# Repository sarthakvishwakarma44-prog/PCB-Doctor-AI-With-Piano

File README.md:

# PCB-Doctor-AI With Piano.
<hr>
<h4>Here i had created a PCB doctor AI with piano, here this was able to do DRC and ERC of PCB and also able to describe the component of PCB's.</h4>
<br><h4>Here this was able to do this things.-</h4>
<ul>
  <li>DRC of physical PCB's.</li>
  <li>ERC of physical PCB's.</li>
  <li>Describe about Components.</li>
  <li>A piano which plays automatic.</li>
</ul>
<hr>
<p><h4>And there is it's source image.-</h4></p>
<h3>Piano</h3>

<hr>
<h3>Servo motor</h3>

<hr>
<h3>PCB's of Camera.</h3>

<hr>

<hr>

<hr>

<hr>

<hr>
<h3>Main Structure</h3>

<hr>
<p><h4>I have less information of KiCad that's why i use google mean they guide me that how to work and i am doing like that. All the PCB's design i have done under the guidance of Google. And for code i have also write it under the guidance of Google.</h4></p>
<br><p><h4>This is work like when we put the PCB in the stand then the camera detect and make imaginary Software PCB and they will done there DRC and ERC in there software and tell the fault in the design of PCB's.</h4></p>
<br><p><h4>And then there is automatic playable piano which was able to play any song automatic without pressing any key by our hands. And we will add SD card to Play any song in it.</h4></p>
<hr>
<p>One more important thing was that i have no 3D printer but my friend live in Honk Kong have this, so my friend will be order all the PCB's in there place and they will also build it there.</p>

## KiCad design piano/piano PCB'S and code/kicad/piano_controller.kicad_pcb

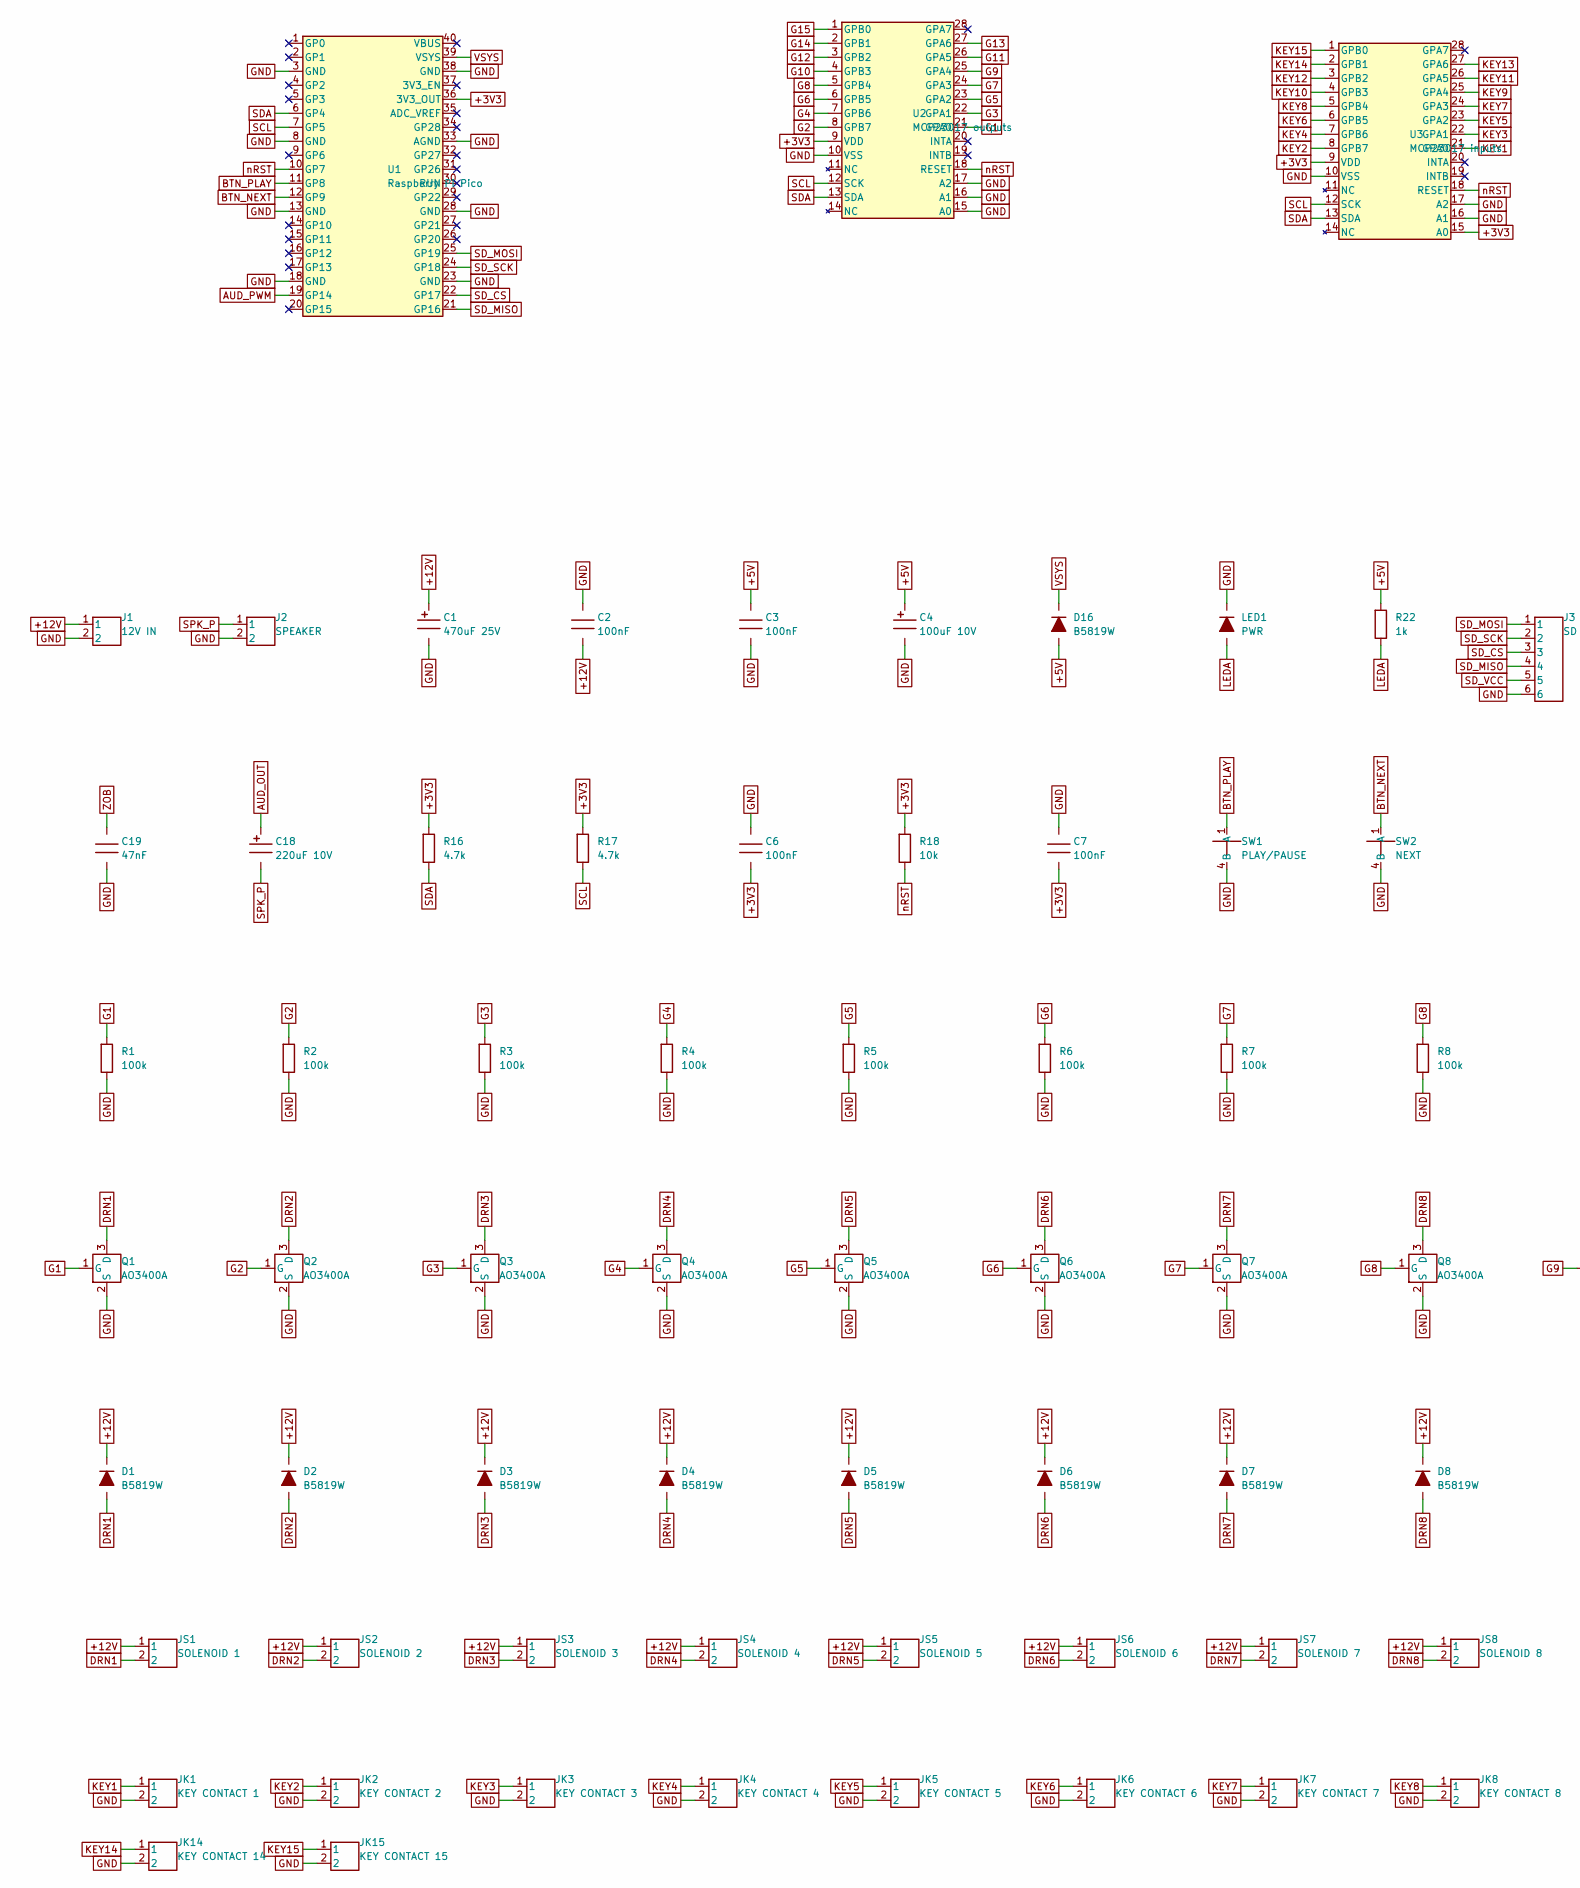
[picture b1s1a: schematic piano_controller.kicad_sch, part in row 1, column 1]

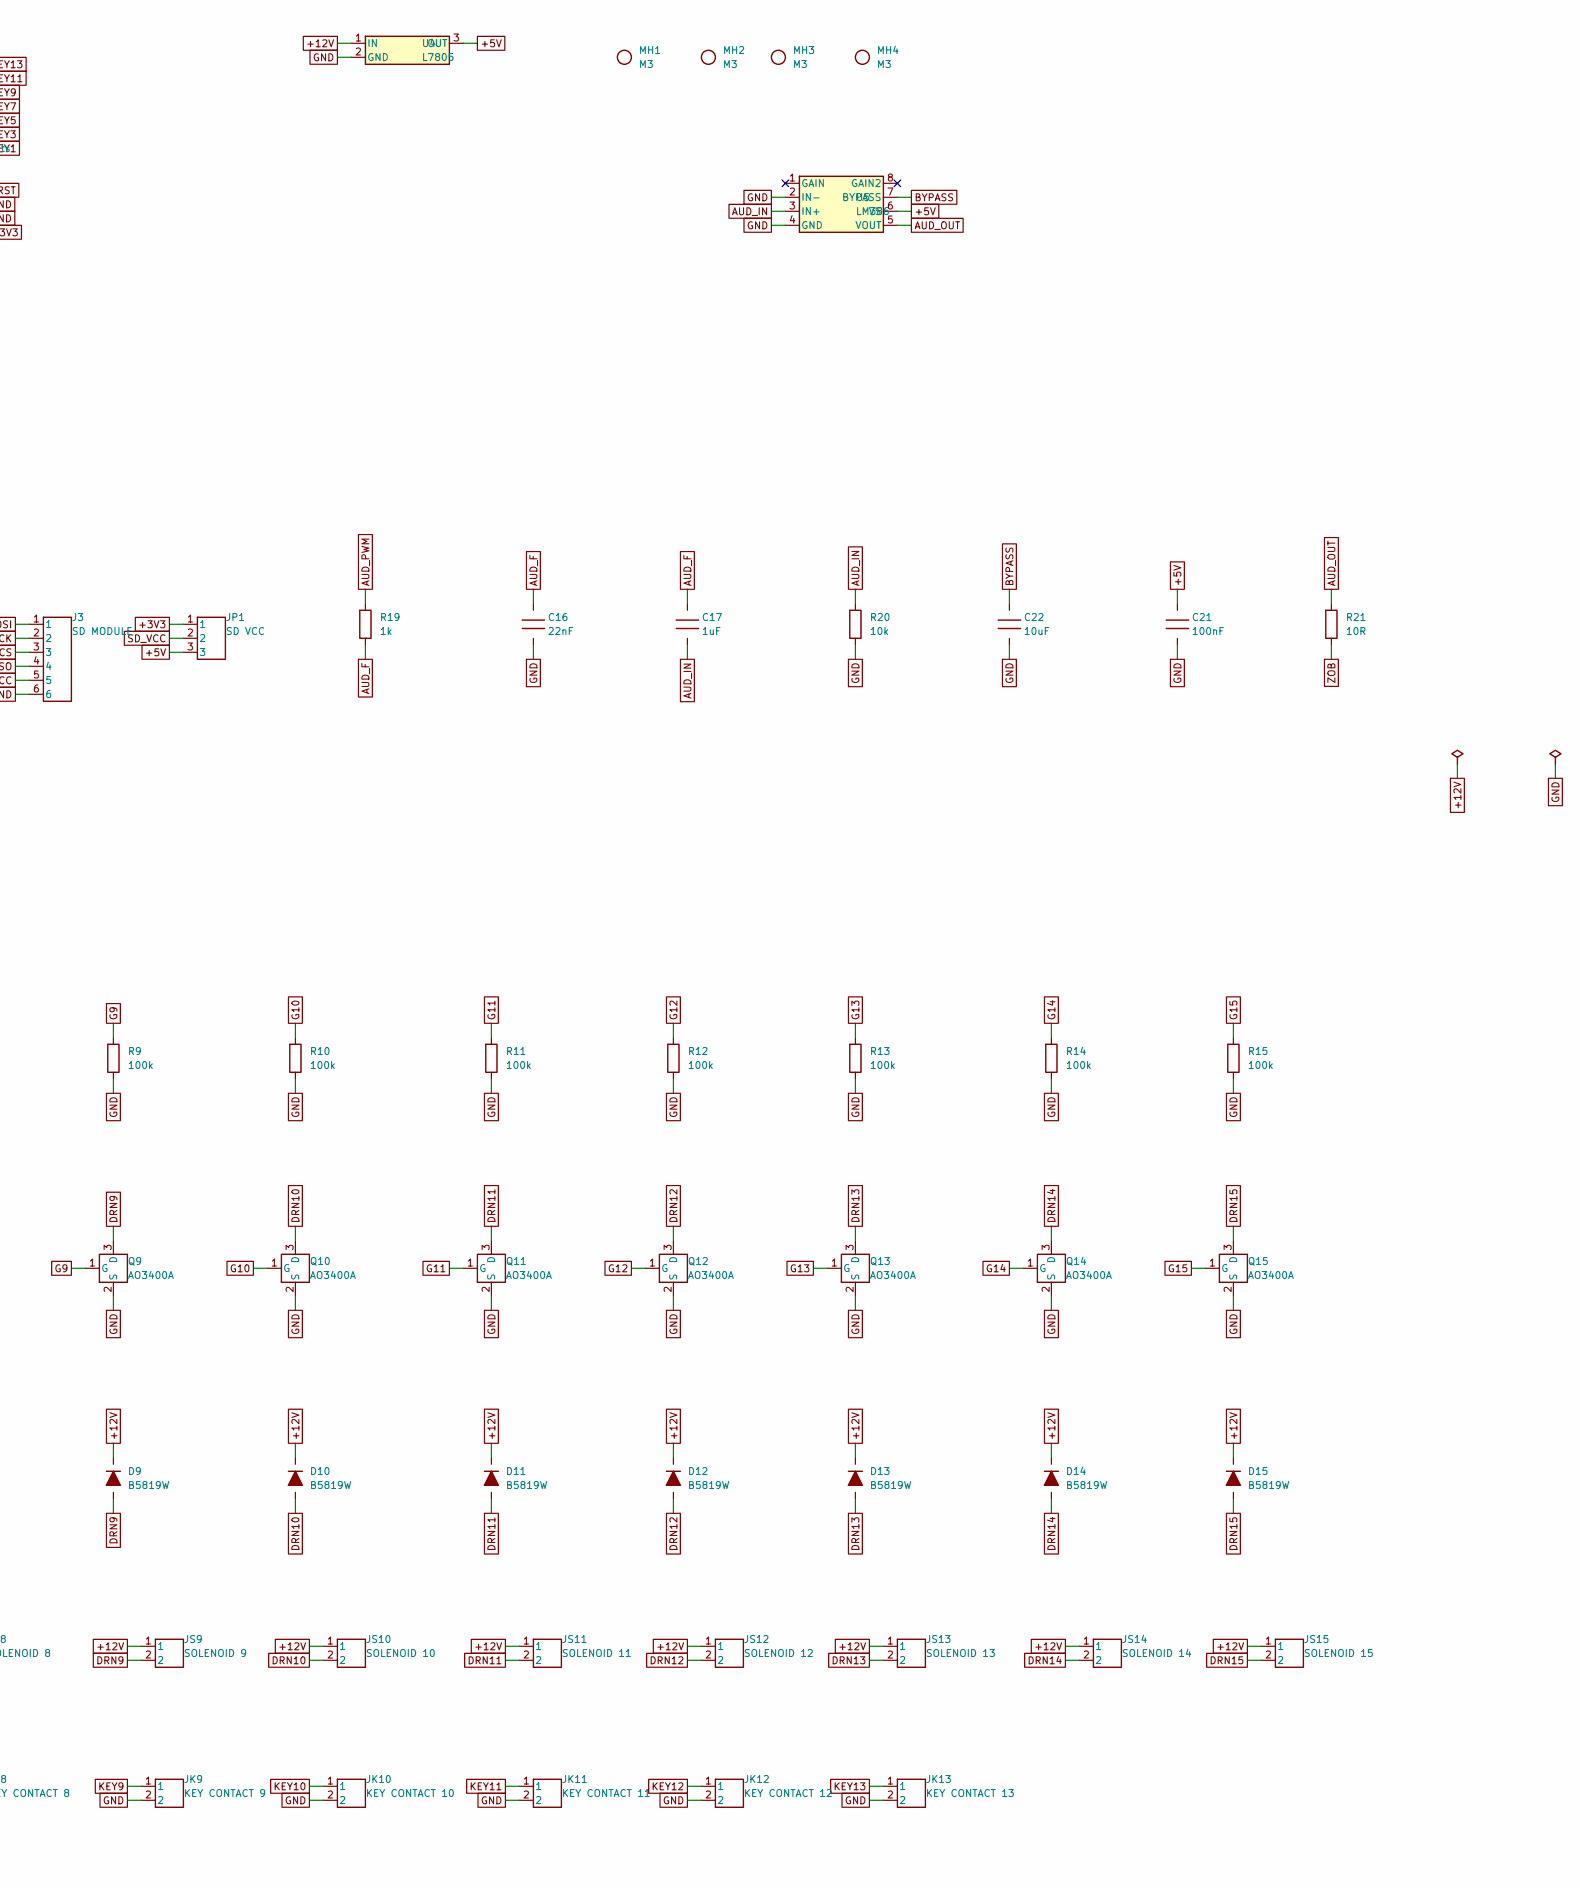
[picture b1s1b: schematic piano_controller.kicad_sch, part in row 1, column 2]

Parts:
C1: 470uF 25V; CP_Radial_D8.0mm_P3.50mm
C2, C3, C6, C7, C21: 100nF; C_0603
C4: 100uF 10V; CP_Radial_D5.0mm_P2.00mm
C16: 22nF; C_0603
C17: 1uF; C_0603
C18: 220uF 10V; CP_Radial_D6.3mm_P2.50mm
C19: 47nF; C_0603
C22: 10uF; C_0603
D1, D2, D3, D4, D5, D6, D7, D8, D9, D10, D11, D12, D13, D14, D15, D16: B5819W; D_SOD-123
J1: 12V IN; TerminalBlock_2P_P5.08mm
J2: SPEAKER; TerminalBlock_2P_P5.08mm
J3: SD MODULE; PinHeader_1x06_P2.54mm
JK1: KEY CONTACT 1; PinHeader_1x02_P2.54mm
JK2: KEY CONTACT 2; PinHeader_1x02_P2.54mm
JK3: KEY CONTACT 3; PinHeader_1x02_P2.54mm
JK4: KEY CONTACT 4; PinHeader_1x02_P2.54mm
JK5: KEY CONTACT 5; PinHeader_1x02_P2.54mm
JK6: KEY CONTACT 6; PinHeader_1x02_P2.54mm
JK7: KEY CONTACT 7; PinHeader_1x02_P2.54mm
JK8: KEY CONTACT 8; PinHeader_1x02_P2.54mm
JK9: KEY CONTACT 9; PinHeader_1x02_P2.54mm
JK10: KEY CONTACT 10; PinHeader_1x02_P2.54mm
JK11: KEY CONTACT 11; PinHeader_1x02_P2.54mm
JK12: KEY CONTACT 12; PinHeader_1x02_P2.54mm
JK13: KEY CONTACT 13; PinHeader_1x02_P2.54mm
JK14: KEY CONTACT 14; PinHeader_1x02_P2.54mm
JK15: KEY CONTACT 15; PinHeader_1x02_P2.54mm
JP1: SD VCC; PinHeader_1x03_P2.54mm
JS1: SOLENOID 1; PinHeader_1x02_P2.54mm
JS2: SOLENOID 2; PinHeader_1x02_P2.54mm
JS3: SOLENOID 3; PinHeader_1x02_P2.54mm
JS4: SOLENOID 4; PinHeader_1x02_P2.54mm
JS5: SOLENOID 5; PinHeader_1x02_P2.54mm
JS6: SOLENOID 6; PinHeader_1x02_P2.54mm
JS7: SOLENOID 7; PinHeader_1x02_P2.54mm
JS8: SOLENOID 8; PinHeader_1x02_P2.54mm
JS9: SOLENOID 9; PinHeader_1x02_P2.54mm
JS10: SOLENOID 10; PinHeader_1x02_P2.54mm
JS11: SOLENOID 11; PinHeader_1x02_P2.54mm
JS12: SOLENOID 12; PinHeader_1x02_P2.54mm
JS13: SOLENOID 13; PinHeader_1x02_P2.54mm
JS14: SOLENOID 14; PinHeader_1x02_P2.54mm
JS15: SOLENOID 15; PinHeader_1x02_P2.54mm
LED1: PWR; LED_0603
MH1, MH2, MH3, MH4: M3; MountingHole_3.2mm_M3
Q1, Q2, Q3, Q4, Q5, Q6, Q7, Q8, Q9, Q10, Q11, Q12, Q13, Q14, Q15: AO3400A; SOT-23
R1, R2, R3, R4, R5, R6, R7, R8, R9, R10, R11, R12, R13, R14, R15: 100k; R_0603
R16, R17: 4.7k; R_0603
R18, R20: 10k; R_0603
R19, R22: 1k; R_0603
R21: 10R; R_0603
SW1: PLAY/PAUSE; SW_PUSH_6mm
SW2: NEXT; SW_PUSH_6mm
U1: Raspberry Pi Pico; RPi_Pico_Socket_2x20
U2: MCP23017 outputs; DIP-28_W7.62mm
U3: MCP23017 inputs; DIP-28_W7.62mm
U4: L7805; TO-220-3_Vertical
U5: LM386; DIP-8_W7.62mm

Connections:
+3V3: C6.2, C7.2, JP1.1, R16.1, R17.1, R18.1, U1.36 (3V3_OUT), U2.9 (VDD), U3.9 (VDD), U3.15 (A0)
+5V: C3.1, C4.1 (+), C21.1, D16.2 (A), JP1.3, R22.1, U4.3 (OUT), U5.6 (VS)
+12V: C1.1 (+), C2.2, D1.1 (K), D2.1 (K), D3.1 (K), D4.1 (K), D5.1 (K), D6.1 (K), D7.1 (K), D8.1 (K), D9.1 (K), D10.1 (K), D11.1 (K), D12.1 (K), D13.1 (K), D14.1 (K), D15.1 (K), J1.1, JS1.1, JS2.1, JS3.1, JS4.1, JS5.1, JS6.1, JS7.1, JS8.1, JS9.1, JS10.1, JS11.1, JS12.1, JS13.1, JS14.1, JS15.1, U4.1 (IN)
AUD_F: C16.1, C17.1, R19.2
AUD_IN: C17.2, R20.1, U5.3 (IN+)
AUD_OUT: C18.1 (+), R21.1, U5.5 (VOUT)
AUD_PWM: R19.1, U1.19 (GP14)
BTN_NEXT: SW2.1 (A), U1.12 (GP9)
BTN_PLAY: SW1.1 (A), U1.11 (GP8)
BYPASS: C22.1, U5.7 (BYPASS)
DRN1: D1.2 (A), JS1.2, Q1.3 (D)
DRN2: D2.2 (A), JS2.2, Q2.3 (D)
DRN3: D3.2 (A), JS3.2, Q3.3 (D)
DRN4: D4.2 (A), JS4.2, Q4.3 (D)
DRN5: D5.2 (A), JS5.2, Q5.3 (D)
DRN6: D6.2 (A), JS6.2, Q6.3 (D)
DRN7: D7.2 (A), JS7.2, Q7.3 (D)
DRN8: D8.2 (A), JS8.2, Q8.3 (D)
DRN9: D9.2 (A), JS9.2, Q9.3 (D)
DRN10: D10.2 (A), JS10.2, Q10.3 (D)
DRN11: D11.2 (A), JS11.2, Q11.3 (D)
DRN12: D12.2 (A), JS12.2, Q12.3 (D)
DRN13: D13.2 (A), JS13.2, Q13.3 (D)
DRN14: D14.2 (A), JS14.2, Q14.3 (D)
DRN15: D15.2 (A), JS15.2, Q15.3 (D)
G1: Q1.1 (G), R1.1, U2.21 (GPA0)
G2: Q2.1 (G), R2.1, U2.8 (GPB7)
G3: Q3.1 (G), R3.1, U2.22 (GPA1)
G4: Q4.1 (G), R4.1, U2.7 (GPB6)
G5: Q5.1 (G), R5.1, U2.23 (GPA2)
G6: Q6.1 (G), R6.1, U2.6 (GPB5)
G7: Q7.1 (G), R7.1, U2.24 (GPA3)
G8: Q8.1 (G), R8.1, U2.5 (GPB4)
G9: Q9.1 (G), R9.1, U2.25 (GPA4)
G10: Q10.1 (G), R10.1, U2.4 (GPB3)
G11: Q11.1 (G), R11.1, U2.26 (GPA5)
G12: Q12.1 (G), R12.1, U2.3 (GPB2)
G13: Q13.1 (G), R13.1, U2.27 (GPA6)
G14: Q14.1 (G), R14.1, U2.2 (GPB1)
G15: Q15.1 (G), R15.1, U2.1 (GPB0)
GND: C1.2 (-), C2.1, C3.2, C4.2 (-), C6.1, C7.1, C16.2, C19.2, C21.2, C22.2, J1.2, J2.2, J3.6, JK1.2, JK2.2, JK3.2, JK4.2, JK5.2, JK6.2, JK7.2, JK8.2, JK9.2, JK10.2, JK11.2, JK12.2, JK13.2, JK14.2, JK15.2, LED1.1 (K), Q1.2 (S), Q2.2 (S), Q3.2 (S), Q4.2 (S), Q5.2 (S), Q6.2 (S), Q7.2 (S), Q8.2 (S), Q9.2 (S), Q10.2 (S), Q11.2 (S), Q12.2 (S), Q13.2 (S), Q14.2 (S), Q15.2 (S), R1.2, R2.2, R3.2, R4.2, R5.2, R6.2, R7.2, R8.2, R9.2, R10.2, R11.2, R12.2, R13.2, R14.2, R15.2, R20.2, SW1.4 (B), SW2.4 (B), U1.3 (GND), U1.8 (GND), U1.13 (GND), U1.18 (GND), U1.23 (GND), U1.28 (GND), U1.33 (AGND), U1.38 (GND), U2.10 (VSS), U2.15 (A0), U2.16 (A1), U2.17 (A2), U3.10 (VSS), U3.16 (A1), U3.17 (A2), U4.2 (GND), U5.2 (IN-), U5.4 (GND)
KEY1: JK1.1, U3.21 (GPA0)
KEY2: JK2.1, U3.8 (GPB7)
KEY3: JK3.1, U3.22 (GPA1)
KEY4: JK4.1, U3.7 (GPB6)
KEY5: JK5.1, U3.23 (GPA2)
KEY6: JK6.1, U3.6 (GPB5)
KEY7: JK7.1, U3.24 (GPA3)
KEY8: JK8.1, U3.5 (GPB4)
KEY9: JK9.1, U3.25 (GPA4)
KEY10: JK10.1, U3.4 (GPB3)
KEY11: JK11.1, U3.26 (GPA5)
KEY12: JK12.1, U3.3 (GPB2)
KEY13: JK13.1, U3.27 (GPA6)
KEY14: JK14.1, U3.2 (GPB1)
KEY15: JK15.1, U3.1 (GPB0)
LEDA: LED1.2 (A), R22.2
SCL: R17.2, U1.7 (GP5), U2.12 (SCK), U3.12 (SCK)
SDA: R16.2, U1.6 (GP4), U2.13 (SDA), U3.13 (SDA)
SD_CS: J3.3, U1.22 (GP17)
SD_MISO: J3.4, U1.21 (GP16)
SD_MOSI: J3.1, U1.25 (GP19)
SD_SCK: J3.2, U1.24 (GP18)
SD_VCC: J3.5, JP1.2
SPK_P: C18.2 (-), J2.1
VSYS: D16.1 (K), U1.39 (VSYS)
ZOB: C19.1, R21.2
nRST: R18.2, U1.10 (GP7), U2.18 (RESET), U3.18 (RESET)

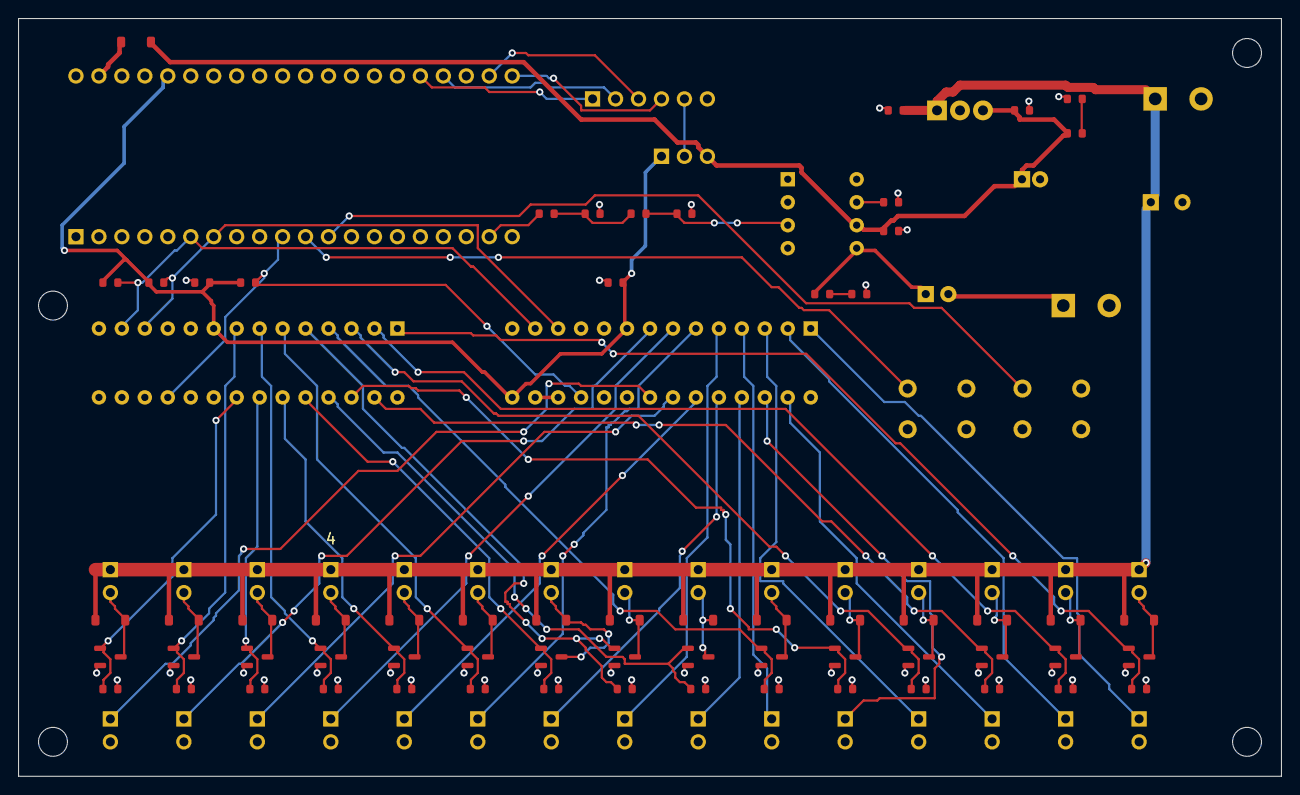
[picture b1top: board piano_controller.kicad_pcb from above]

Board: 2 copper layers, 139.7 x 83.8 mm, 111 parts (0 on the bottom side), 68 nets.

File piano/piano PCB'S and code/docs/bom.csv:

quantity,description,references
1,Raspberry Pi Pico (no headers) + two 1x20 female 2.54 mm sockets,U1
2,MCP23017-E/SP skinny DIP-28 (use a socket),U2 U3
1,L7805CV TO-220 regulator,U4
1,LM386N-1 DIP-8 (use a socket),U5
1,Screw terminal 2 pin 5.08 mm,J1
1,"Screw terminal 2 pin 5.08 mm, 8 ohm speaker 0.5-2 W",J2
1,Electrolytic 470uF 25V radial D8 P3.5,C1
5,Capacitor 100nF 50V 0603,C2 C3 C21 C6 C7
1,Electrolytic 100uF 10V radial D5 P2.0,C4
16,Schottky diode 40V 1A SOD-123,D16 D1 D2 D3 D4 D5 D6 D7 D8 D9 D10 D11 D12 D13 D14 D15
1,LED 0603 any colour,LED1
2,Resistor 1k 0603,R22 R19
1,1x06 pin header 2.54 mm,J3
1,1x03 pin header 2.54 mm + jumper,JP1
1,Capacitor 22nF 0603,C16
1,Capacitor 1uF 0603,C17
2,Resistor 10k 0603,R20 R18
1,Capacitor 10uF 10V 0603,C22
1,Resistor 10 ohm 0603,R21
1,Capacitor 47nF 0603,C19
1,Electrolytic 220uF 10V radial D6.3 P2.5,C18
2,Resistor 4.7k 0603,R16 R17
2,6 mm tactile switch,SW1 SW2
4,M3 mounting hole (screw M3),MH1 MH2 MH3 MH4
15,N-channel MOSFET 30V 5.7A SOT-23,Q1 Q2 Q3 Q4 Q5 Q6 Q7 Q8 Q9 Q10 Q11 Q12 Q13 Q14 Q15
15,Resistor 100k 0603,R1 R2 R3 R4 R5 R6 R7 R8 R9 R10 R11 R12 R13 R14 R15
30,1x02 pin header 2.54 mm (Dupont),JS1 JK1 JS2 JK2 JS3 JK3 JS4 JK4 JS5 JK5 JS6 JK6 JS7 JK7 JS8 JK8 JS9 JK9 JS10 JK10 JS11 JK11 JS12 JK12 JS13 JK13 JS14 JK14 JS15 JK15

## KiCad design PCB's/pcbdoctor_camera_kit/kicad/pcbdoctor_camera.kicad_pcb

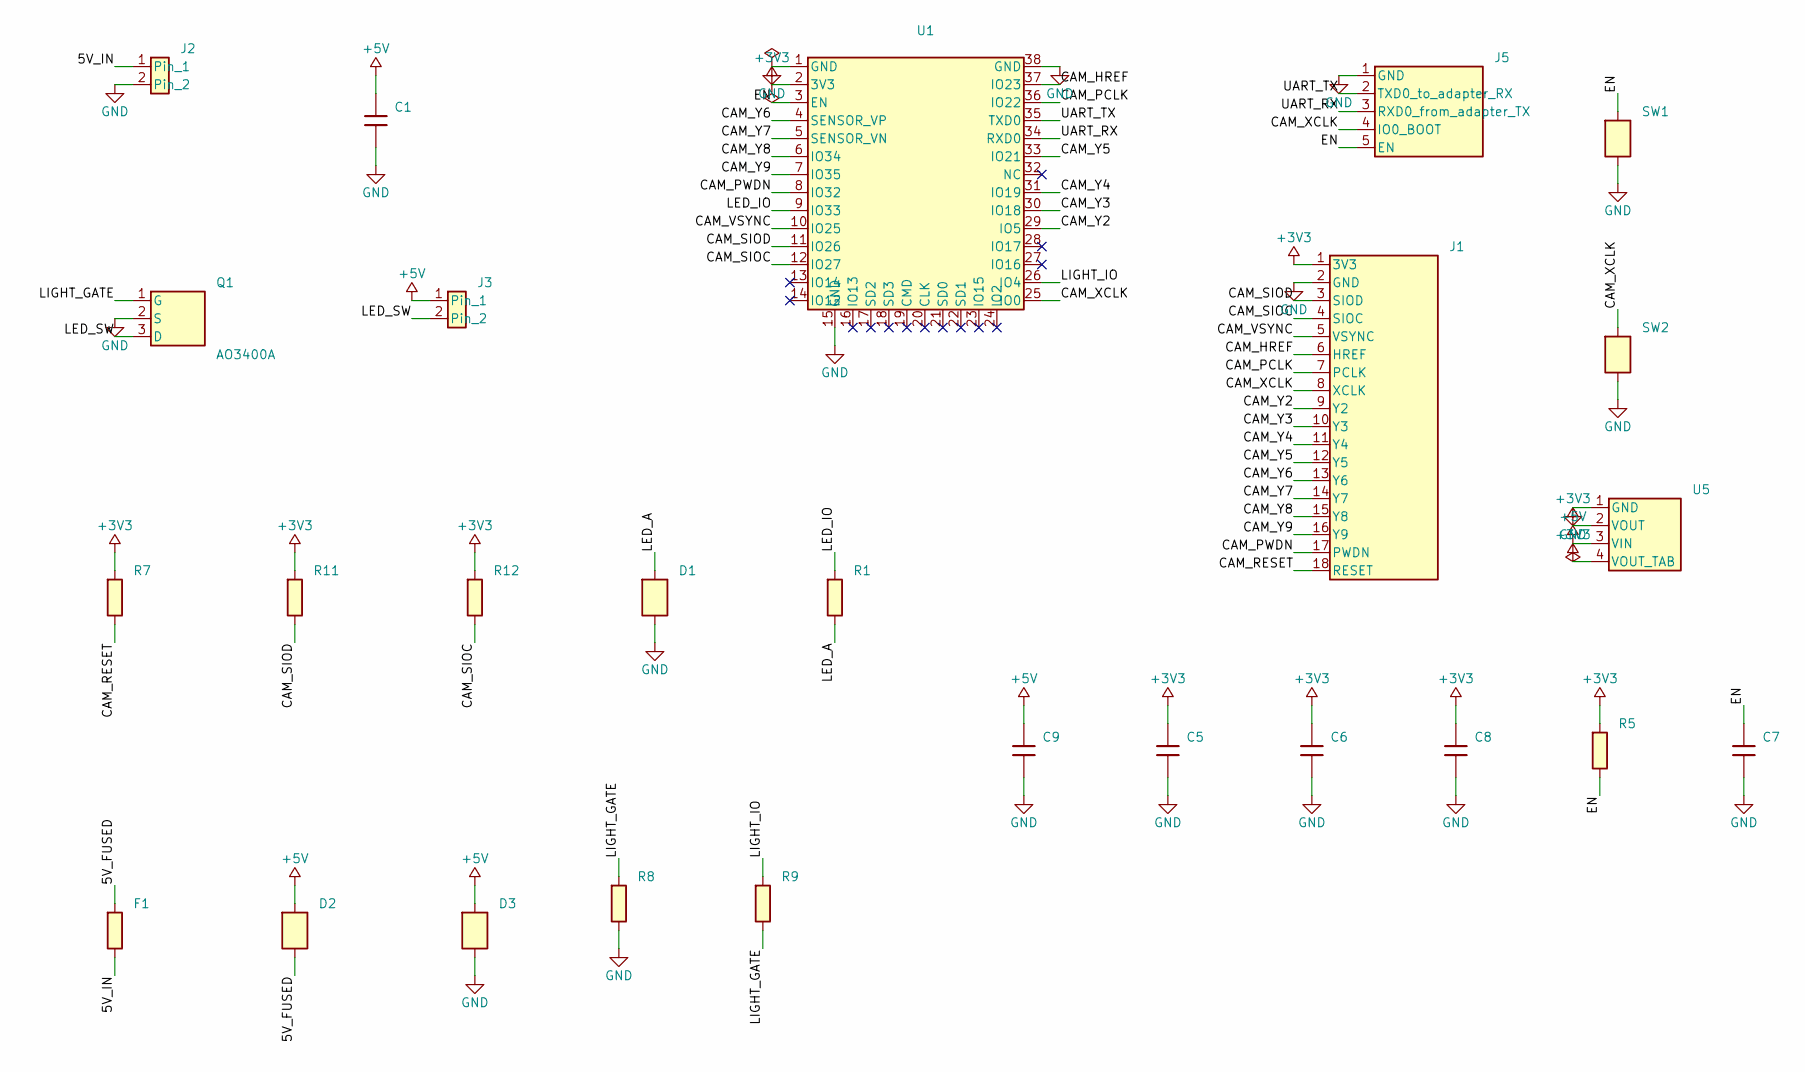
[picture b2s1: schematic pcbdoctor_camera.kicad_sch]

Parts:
C1, C6, C9: 10uF 10V; C_0805
C5: 22uF tantalum; CP_Tantalum_A_3216
C7: 1uF; C_0805
C8: 100nF; C_0805
D1: STATUS; LED_D3.0mm
D2: SS14; D_SMA
D3: SMAJ5.0A TVS; D_SMA
F1: PTC ~1.1A (verify); Fuse_1206
J1: CAMERA (DVP) header; PinHeader_1x18_P2.54mm
J2: 5V IN from machine; PinHeader_1x02_P2.54mm
J3: LED LIGHT (+5V / switched -); PinHeader_1x02_P2.54mm
J5: UART programming; PinHeader_1x05_P2.54mm
Q1: AO3400A; SOT-23
R1: 1k; R_0805
R5, R7, R8: 10k; R_0805
R9: 100; R_0805
R11, R12: 4.7k; R_0805
SW1: EN (reset); SW_Push_6mm
SW2: BOOT (IO0); SW_Push_6mm
U1: ESP32-WROOM-32E-N8R2 (PSRAM); ESP32_WROOM_32E_reconstructed
U5: AMS1117-3.3; SOT-223

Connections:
+3V3: C5.1, C6.1, C8.1, J1.1 (3V3), R5.1, R7.1, R11.1, R12.1, U1.2 (3V3), U5.2 (VOUT), U5.4 (VOUT_TAB)
+5V: C1.1, C9.1, D2.1 (K), D3.1 (K), J3.1, U5.3 (VIN)
/5V_FUSED: D2.2 (A), F1.1
/5V_IN: F1.2, J2.1
/CAM_HREF: J1.6 (HREF), U1.37 (IO23)
/CAM_PCLK: J1.7 (PCLK), U1.36 (IO22)
/CAM_PWDN: J1.17 (PWDN), U1.8 (IO32)
/CAM_RESET: J1.18 (RESET), R7.2
/CAM_SIOC: J1.4 (SIOC), R12.2, U1.12 (IO27)
/CAM_SIOD: J1.3 (SIOD), R11.2, U1.11 (IO26)
/CAM_VSYNC: J1.5 (VSYNC), U1.10 (IO25)
/CAM_XCLK: J1.8 (XCLK), J5.4 (IO0_BOOT), SW2.1, U1.25 (IO0)
/CAM_Y2: J1.9 (Y2), U1.29 (IO5)
/CAM_Y3: J1.10 (Y3), U1.30 (IO18)
/CAM_Y4: J1.11 (Y4), U1.31 (IO19)
/CAM_Y5: J1.12 (Y5), U1.33 (IO21)
/CAM_Y6: J1.13 (Y6), U1.4 (SENSOR_VP)
/CAM_Y7: J1.14 (Y7), U1.5 (SENSOR_VN)
/CAM_Y8: J1.15 (Y8), U1.6 (IO34)
/CAM_Y9: J1.16 (Y9), U1.7 (IO35)
/EN: C7.1, J5.5 (EN), R5.2, SW1.1, U1.3 (EN)
/LED_A: D1.2 (A), R1.2
/LED_IO: R1.1, U1.9 (IO33)
/LED_SW: J3.2, Q1.3 (D)
/LIGHT_GATE: Q1.1 (G), R8.1, R9.2
/LIGHT_IO: R9.1, U1.26 (IO4)
/UART_RX: J5.3 (RXD0_from_adapter_TX), U1.34 (RXD0)
/UART_TX: J5.2 (TXD0_to_adapter_RX), U1.35 (TXD0)
GND: C1.2, C5.2, C6.2, C7.2, C8.2, C9.2, D1.1 (K), D3.2 (A), J1.2 (GND), J2.2, J5.1 (GND), Q1.2 (S), R8.2, SW1.2, SW2.2, U1.1 (GND), U1.15 (GND), U1.38 (GND), U5.1 (GND)

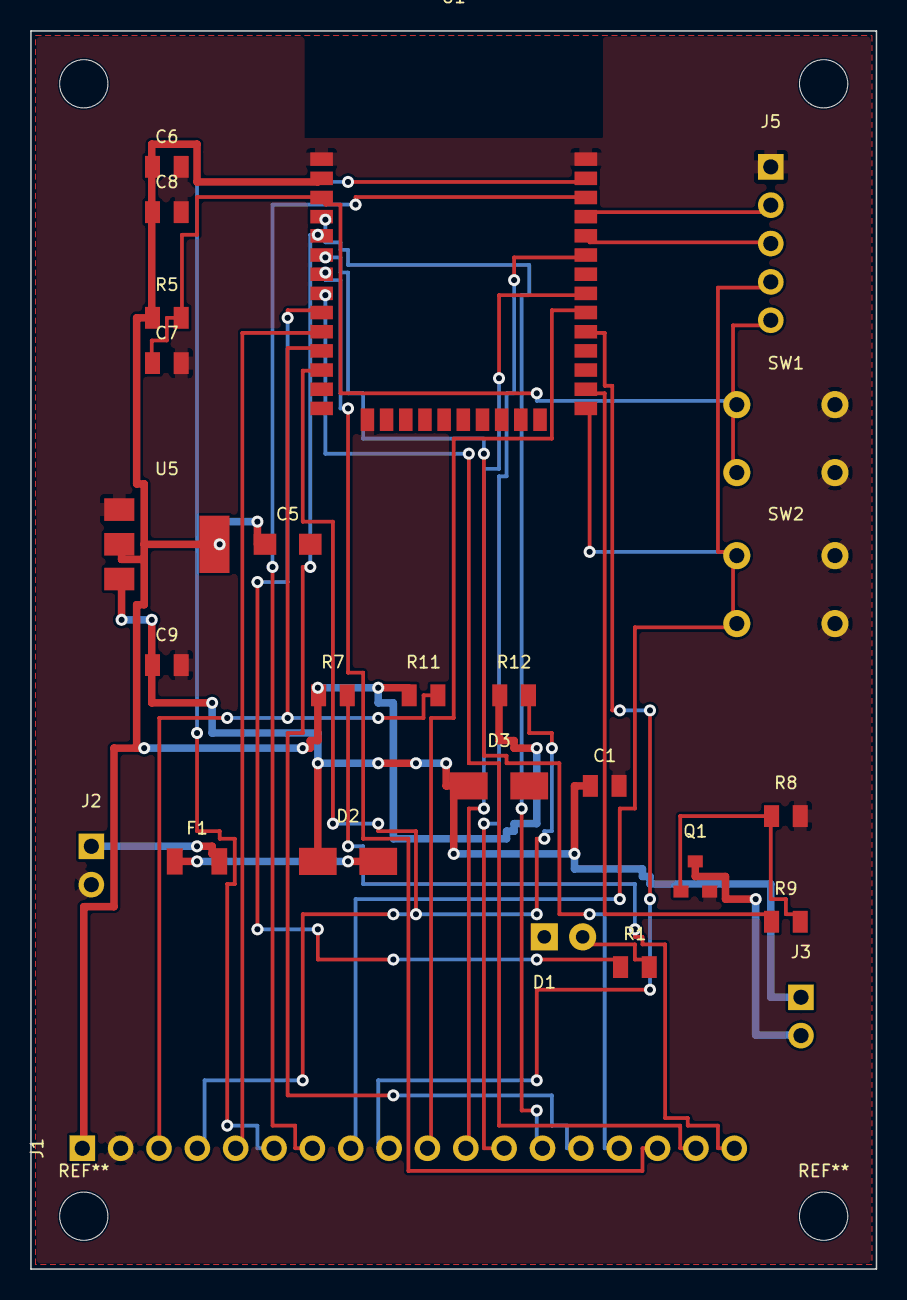
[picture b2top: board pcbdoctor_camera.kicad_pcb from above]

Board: 2 copper layers, 56.0 x 82.0 mm, 26 parts (0 on the bottom side), 29 nets.

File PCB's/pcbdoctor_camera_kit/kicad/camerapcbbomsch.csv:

"Reference","Qty","Value","DNP","Exclude from BOM","Exclude from Board","Exclude from Simulation","Exclude from Position Files","Footprint","Datasheet","#","Description"
"C1,C6,C9","3","10uF 10V","","","","","${EXCLUDE_FROM_POS_FILES}","PCBDoctor:C_0805","","1",""
"C5","1","22uF tantalum","","","","","${EXCLUDE_FROM_POS_FILES}","PCBDoctor:CP_Tantalum_A_3216","","2",""
"C7","1","1uF","","","","","${EXCLUDE_FROM_POS_FILES}","PCBDoctor:C_0805","","3",""
"C8","1","100nF","","","","","${EXCLUDE_FROM_POS_FILES}","PCBDoctor:C_0805","","4",""
"D1","1","STATUS","","","","","${EXCLUDE_FROM_POS_FILES}","PCBDoctor:LED_D3.0mm","","5",""
"D2","1","SS14","","","","","${EXCLUDE_FROM_POS_FILES}","PCBDoctor:D_SMA","","6",""
"D3","1","SMAJ5.0A TVS","","","","","${EXCLUDE_FROM_POS_FILES}","PCBDoctor:D_SMA","","7",""
"F1","1","PTC ~1.1A (verify)","","","","","${EXCLUDE_FROM_POS_FILES}","PCBDoctor:Fuse_1206","","8",""
"J1","1","CAMERA (DVP) header","","","","","${EXCLUDE_FROM_POS_FILES}","PCBDoctor:PinHeader_1x18_P2.54mm","","9",""
"J2","1","5V IN from machine","","","","","${EXCLUDE_FROM_POS_FILES}","PCBDoctor:PinHeader_1x02_P2.54mm","","10",""
"J3","1","LED LIGHT (+5V / switched -)","","","","","${EXCLUDE_FROM_POS_FILES}","PCBDoctor:PinHeader_1x02_P2.54mm","","11",""
"J5","1","UART programming","","","","","${EXCLUDE_FROM_POS_FILES}","PCBDoctor:PinHeader_1x05_P2.54mm","","12",""
"Q1","1","AO3400A","","","","","${EXCLUDE_FROM_POS_FILES}","PCBDoctor:SOT-23","","13",""
"R1","1","1k","","","","","${EXCLUDE_FROM_POS_FILES}","PCBDoctor:R_0805","","14",""
"R5,R7,R8","3","10k","","","","","${EXCLUDE_FROM_POS_FILES}","PCBDoctor:R_0805","","15",""
"R9","1","100","","","","","${EXCLUDE_FROM_POS_FILES}","PCBDoctor:R_0805","","16",""
"R11,R12","2","4.7k","","","","","${EXCLUDE_FROM_POS_FILES}","PCBDoctor:R_0805","","17",""
"SW1","1","EN (reset)","","","","","${EXCLUDE_FROM_POS_FILES}","PCBDoctor:SW_Push_6mm","","18",""
"SW2","1","BOOT (IO0)","","","","","${EXCLUDE_FROM_POS_FILES}","PCBDoctor:SW_Push_6mm","","19",""
"U1","1","ESP32-WROOM-32E-N8R2 (PSRAM)","","","","","${EXCLUDE_FROM_POS_FILES}","PCBDoctor:ESP32_WROOM_32E_reconstructed","","20",""
"U5","1","AMS1117-3.3","","","","","${EXCLUDE_FROM_POS_FILES}","PCBDoctor:SOT-223","","21",""

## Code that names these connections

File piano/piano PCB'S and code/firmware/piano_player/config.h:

#pragma once
#include <Arduino.h>

constexpr uint8_t KEY_COUNT = 15;

constexpr uint8_t PIN_SDA = 4;
constexpr uint8_t PIN_SCL = 5;
constexpr uint8_t PIN_RESET = 7;
constexpr uint8_t PIN_PLAY = 8;
constexpr uint8_t PIN_NEXT = 9;
constexpr uint8_t PIN_AUDIO = 14;
constexpr uint8_t PIN_SD_MISO = 16;
constexpr uint8_t PIN_SD_CS = 17;
constexpr uint8_t PIN_SD_SCK = 18;
constexpr uint8_t PIN_SD_MOSI = 19;

constexpr uint8_t ADDR_OUT = 0x20;
constexpr uint8_t ADDR_IN = 0x21;

constexpr uint8_t FIRST_NOTE = 60;
constexpr uint8_t MAX_POLY = 6;
constexpr uint16_t MAX_HOLD_MS = 2500;
constexpr uint16_t MIN_GAP_MS = 35;
constexpr uint16_t SENSE_PERIOD_MS = 2;
constexpr uint16_t FAULT_MS = 150;
constexpr uint16_t LOOKAHEAD_MS = 160;
constexpr uint16_t PREROLL_MS = 120;
constexpr uint16_t SONG_GAP_MS = 1500;
constexpr uint16_t DEBOUNCE_MS = 35;

constexpr int16_t LEAD_START_MS = 12;
constexpr int16_t LEAD_MIN_MS = 4;
constexpr int16_t LEAD_MAX_MS = 60;

constexpr bool SYNTH_ENABLED = true;
constexpr uint8_t MAX_SONGS = 48;
